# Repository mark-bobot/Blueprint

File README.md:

# MarkPad
A 4-key macropad with a rotary encoder, built with a Seeeduino XIAO microcontroller. I made this for the Hack Club Blueprint project. I wanted a small dedicated pad for shortcuts I actually use day-to-day (copy, paste, mute, and a shortcut to open claude). The encoder controls volume.

I am new to electronics design so this was a very fun interesting project for me to work on.

## How to use it

Plug it in over USB-C. The XIAO runs KMK firmware (CircuitPython), so you can remap the keys by editing `main.py`. The default layout is:

- **SW2**: Copy (⌘C)
- **SW3**: Paste (⌘V)
- **SW4**: Mic mute (⌘⇧M)
- **SW5**: Opens claude in a new tab
- **Encoder twist**: Volume up/down
- **Encoder press**: Mute

## CAD

The case is a single 3D-printed part. There’s no lid as it's an open-top design. The switches and encoder are exposed on top, so one part is all you need. I designed it in fusion 360.

## PCB

Designed in KiCad. The encoder is at the top, XIAO in the middle, four switches in a column below.

**Schematic**

## Firmware

KMK on CircuitPython. The main file is `Firmware/main.py`. It uses direct-wired scanning (no matrix) since there are only 5 inputs. The encoder is handled by the `EncoderHandler` module.

## BOM

| Qty | Part | Price | Notes | Link |
|-----|------|-------|-------|------|
| 4 | Cherry MX-compatible switch | £5.19 | 10x Cherry MX Blue Switches | [Amazon](https://amzn.eu/d/0bAqqb6x) |
| 4 | Keycaps (1u) | £5.69 | 5x White keycaps | [Amazon](https://amzn.eu/d/0er6c40q) |
| 1 | EC11 rotary encoder | £3.99 | 1x 360 degree rotary encoder | [Amazon](https://amzn.eu/d/0evqXiXo) |
| 1 | Encoder knob | — | Included in the EC11 rotary encoder | — |
| 1 | Seeeduino XIAO (SAMD21) | £5.44 | USB-C microcontroller | [Seeed Studio](https://www.seeedstudio.com/Seeeduino-XIAO-Arduino-Microcontroller-SAMD21-Cortex-M0+-p-4426.html) |
| 1 | Custom PCB | — | Order from JLCPCB using gerbers | [JLCPCB](https://jlcpcb.com/) |
| 1 | 3D-printed case | — | PLA or PETG | N/A |

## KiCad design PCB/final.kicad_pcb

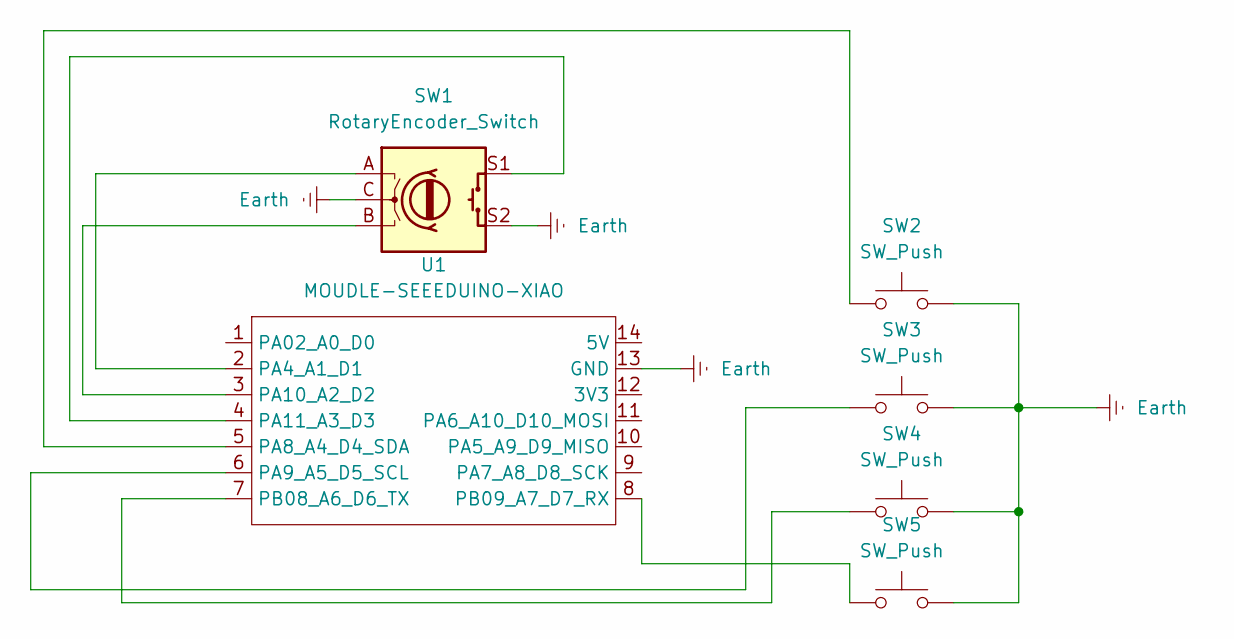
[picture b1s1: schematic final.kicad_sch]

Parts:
SW1: RotaryEncoder_Switch; RotaryEncoder_Alps_EC11E-Switch_Vertical_H20mm
SW2, SW3, SW4, SW5: SW_Push; SW_Cherry_MX_1.00u_PCB
U1: MOUDLE-SEEEDUINO-XIAO; XIAO-Generic-Hybrid-14P-2.54-21X17.8MM

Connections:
Earth: SW1.C, SW1.S2, SW2.2, SW3.2, SW4.2, SW5.2, U1.13 (GND)
unnamed: SW1.A, U1.2 (PA4_A1_D1)
unnamed: SW2.1, U1.5 (PA8_A4_D4_SDA)
unnamed: SW3.1, U1.6 (PA9_A5_D5_SCL)
unnamed: SW1.B, U1.3 (PA10_A2_D2)
unnamed: SW1.S1, U1.4 (PA11_A3_D3)
unnamed: SW4.1, U1.7 (PB08_A6_D6_TX)
unnamed: SW5.1, U1.8 (PB09_A7_D7_RX)

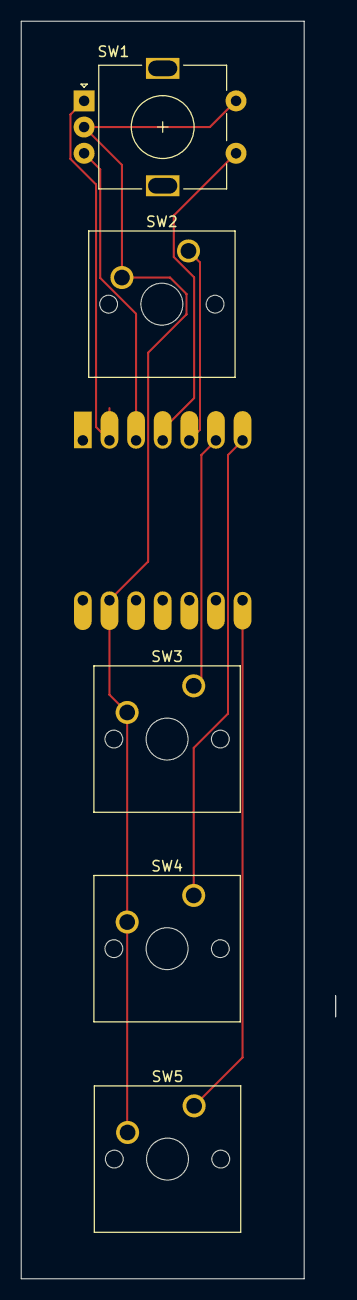
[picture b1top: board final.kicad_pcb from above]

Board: 2 copper layers, 30.0 x 120.0 mm, 6 parts (1 on the bottom side), 8 nets.

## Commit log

2026-04-13 fresh start
2026-04-13 Replace markdown images with HTML img tags
    Updated images in README.md to use <img> tags instead of markdown syntax.
2026-04-13 Update pin assignments for keyboard and encoder
